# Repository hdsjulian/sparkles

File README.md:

This repo theoretically contains everything to build, assemble and run the sparkling forests light installation. In practice it would require much more documentation which i'm too lazy for right now, and maybe the casing-folder also has some pretty rogue STL files that don't belong there.

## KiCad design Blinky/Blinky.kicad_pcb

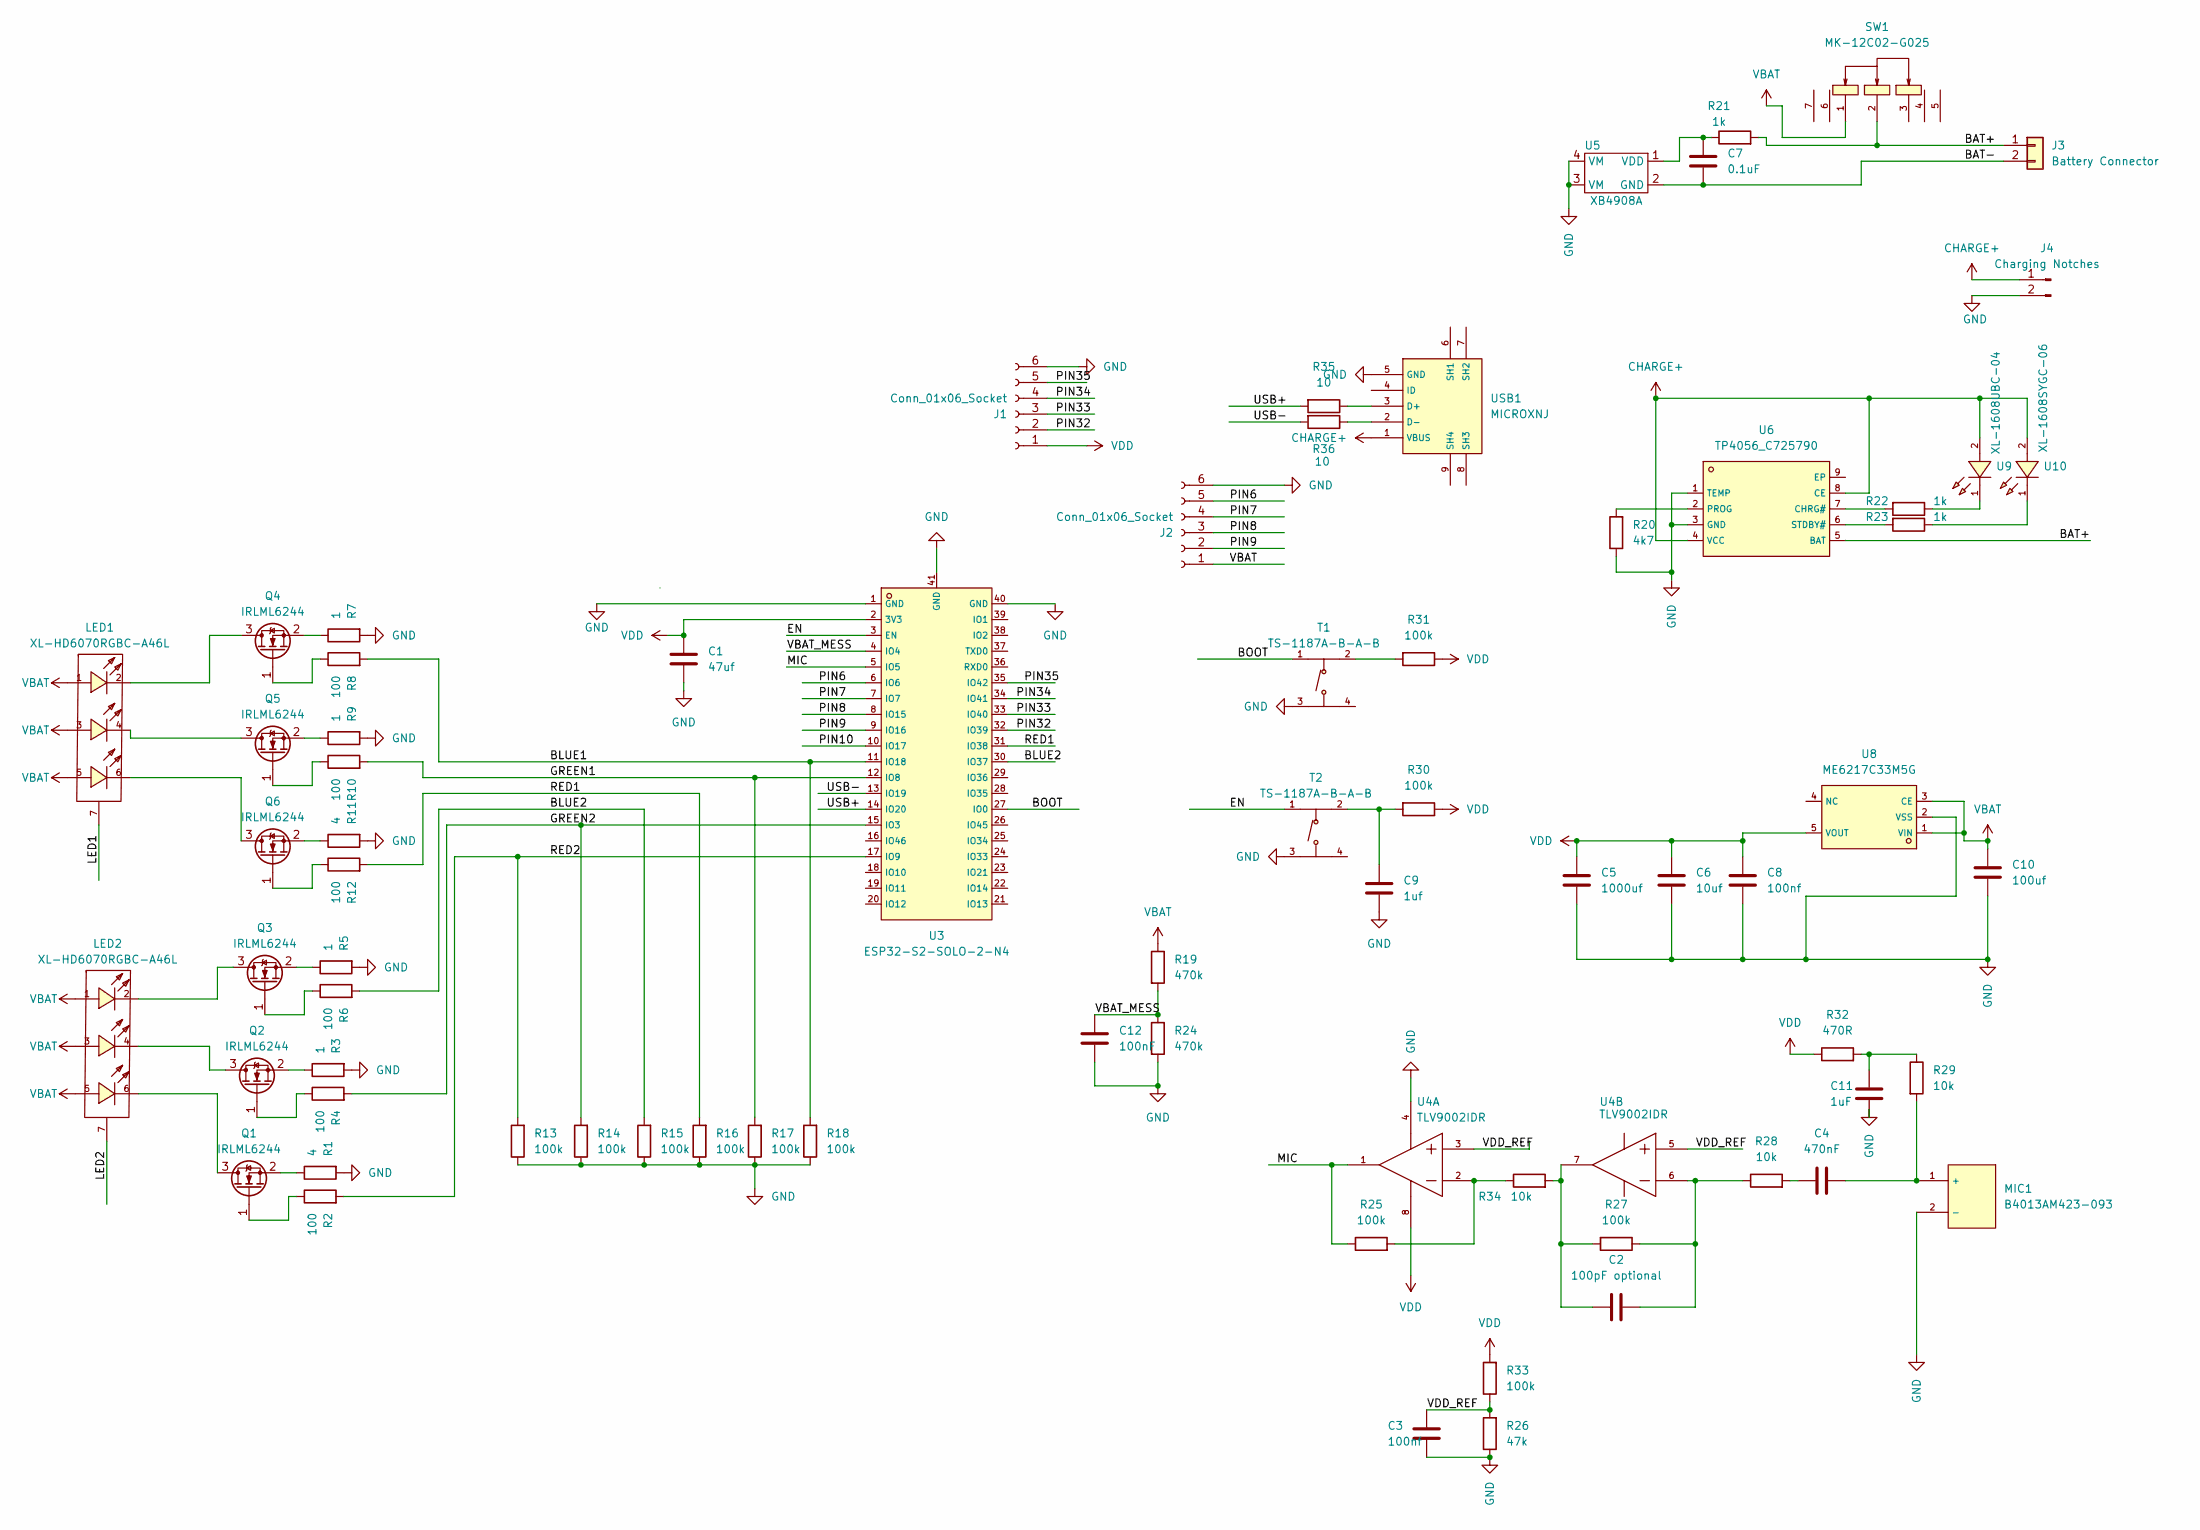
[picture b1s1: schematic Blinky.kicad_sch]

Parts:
C1: 47uf; C_0603_1608Metric
C2: 100pF optional; C_0603_1608Metric
C3, C8: 100nf; C_0603_1608Metric
C4: 470nF; C_0603_1608Metric
C5: 1000uf; CAP-SMD_BD8.0-L8.3-W8.3-FD
C6: 10uf; C_0603_1608Metric
C7: 0.1uF; C_0603_1608Metric
C9: 1uf; C_0603_1608Metric
C10: 100uf; CASE-B_3528
C11: 1uF; C_0603_1608Metric
C12: 100nF; C_0603_1608Metric
J1, J2: Conn_01x06_Socket; HDR-TH_6P-P2.54-V-F
J3: Battery Connector; JST_PH_B2B-PH-K_1x02_P2.00mm_Vertical
J4: Charging Notches; ChargingNotches
LED1, LED2: XL-HD6070RGBC-A46L; LED-SMD_XL-HD6070RGBC-A46L; LCSC C5349977
MIC1: B4013AM423-093; MIC-TH_BD6.0_B6027AP383-056; LCSC C233790
Q1, Q2, Q3, Q4, Q5, Q6: IRLML6244; SOT-23
R1, R11: 4; R_0603_1608Metric
R2, R4, R6, R8, R10, R12: 100; R_0603_1608Metric
R3, R5, R7, R9: 1; R_0603_1608Metric
R13, R14, R15, R16, R17, R18, R25, R27, R30, R31, R33: 100k; R_0603_1608Metric
R19, R24: 470k; R_0603_1608Metric
R20: 4k7; R_0603_1608Metric
R21, R22, R23: 1k; R_0603_1608Metric
R26: 47k; R_0603_1608Metric
R28, R29, R34: 10k; R_0603_1608Metric
R32: 470R; R_0603_1608Metric
R35, R36: 10; R_0603_1608Metric
SW1: MK-12C02-G025; SW-SMD_MK-12C02-G025; LCSC C778186
T1, T2: TS-1187A-B-A-B; SW-SMD_4P-L5.1-W5.1-P3.70-LS6.5-TL-2; LCSC C318884
U3: ESP32-S2-SOLO-2-N4; WIRELM-SMD_ESP32-S3-WROOM-1; LCSC C3040594
U4: TLV9002IDR; SOIC-8_L4.9-W3.9-P1.27-LS6.0-BL; LCSC C398360
U5: XB4908A
U6: TP4056_C725790; ESOP-8_L4.9-W3.9-P1.27-LS6.0-BL-EP; LCSC C725790
U8: ME6217C33M5G; SOT-23-5_L3.0-W1.7-P0.95-LS2.8-BR; LCSC C427602
U9: XL-1608UBC-04; LED0603-RD_BLUE; LCSC C965807
U10: XL-1608SYGC-06; LED0603-RD_GREEN; LCSC C965805
USB1: MICROXNJ; MICRO-USB-SMD_MICROXNJ; LCSC C404969

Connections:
/BAT+: J3.1, R21.2, SW1.2, U6.5 (BAT)
/BAT-: C7.2, J3.2, U5.2 (GND)
/BLUE1: R8.2, R18.2, U3.11 (IO18)
/BLUE2: R6.2, R15.2, U3.30 (IO37)
/BOOT: T1.1 (A), U3.27 (IO0)
/EN: T2.1 (A), U3.3 (EN)
/GREEN1: R10.2, R17.2, U3.12 (IO8)
/GREEN2: R4.2, R14.2, U3.15 (IO3)
/LED1: LED1.7
/LED2: LED2.7
/MIC: R25.1, U3.5 (IO5), U4.1 (OUT1)
/PIN6: J2.5, U3.6 (IO6)
/PIN7: J2.4, U3.7 (IO7)
/PIN8: J2.3, U3.8 (IO15)
/PIN9: J2.2, U3.9 (IO16)
/PIN10: U3.10 (IO17)
/PIN32: J1.2, U3.32 (IO39)
/PIN33: J1.3, U3.33 (IO40)
/PIN34: J1.4, U3.34 (IO41)
/PIN35: J1.5, U3.35 (IO42)
/RED1: R12.2, R16.2, U3.31 (IO38)
/RED2: R2.2, R13.2, U3.17 (IO9)
/USB+: R35.2, U3.14 (IO20)
/USB-: R36.2, U3.13 (IO19)
/VBAT_MESS: C12.2, R19.2, R24.1, U3.4 (IO4)
/VDD_REF: C3.1, R26.2, R33.1, U4.3 (IN1+), U4.5 (IN2+)
CHARGE+: J4.1, U6.4 (VCC), U6.8 (CE), U9.2 (A), U10.2 (A), USB1.1 (VBUS)
GND: C1.1, C3.2, C5.2, C6.1, C8.1, C9.1, C10.2, C11.2, C12.1, J1.6, J2.6, J4.2, MIC1.2 (-), R1.2, R3.2, R5.2, R7.2, R9.2, R11.2, R13.1, R14.1, R15.1, R16.1, R17.1, R18.1, R20.1, R24.2, R26.1, T1.3 (C), T2.3 (C), U3.1 (GND), U3.40 (GND), U3.41 (GND), U4.4 (V-), U5.3 (VM), U5.4 (VM), U6.1 (TEMP), U6.3 (GND), U8.2 (VSS), USB1.5 (GND)
unnamed: C4.1, R28.2
unnamed: C11.1, R29.1, R32.2
unnamed: C4.2, MIC1.1 (+), R29.2
unnamed: LED2.6, Q1.3 (D)
unnamed: Q1.1 (G), R2.1
unnamed: Q1.2 (S), R1.1
unnamed: LED2.4, Q2.3 (D)
unnamed: Q2.1 (G), R4.1
unnamed: Q2.2 (S), R3.1
unnamed: LED2.2, Q3.3 (D)
unnamed: Q3.1 (G), R6.1
unnamed: Q3.2 (S), R5.1
unnamed: LED1.2, Q4.3 (D)
unnamed: Q4.1 (G), R8.1
unnamed: Q4.2 (S), R7.1
unnamed: LED1.4, Q5.3 (D)
unnamed: Q5.1 (G), R10.1
unnamed: Q5.2 (S), R9.1
unnamed: LED1.6, Q6.3 (D)
unnamed: Q6.1 (G), R12.1
unnamed: Q6.2 (S), R11.1
unnamed: R31.2, T1.2 (B)
unnamed: C9.2, R30.2, T2.2 (B)
unnamed: R25.2, R34.1, U4.2 (IN1-)
unnamed: C2.2, R27.1, R28.1, U4.6 (IN2-)
unnamed: C2.1, R27.2, R34.2, U4.7 (OUT2)
unnamed: C7.1, R21.1, U5.1 (VDD)
unnamed: R22.2, U6.7 (CHRG#)
unnamed: R20.2, U6.2 (PROG)
unnamed: R23.2, U6.6 (STDBY#)
unnamed: R22.1, U9.1 (K)
unnamed: R23.1, U10.1 (K)
unnamed: R35.1, USB1.3 (D+)
unnamed: R36.1, USB1.2 (D-)
VBAT: C10.1, J2.1, LED1.1, LED1.3, LED1.5, LED2.1, LED2.3, LED2.5, R19.1, SW1.1, U8.1 (VIN), U8.3 (CE)
VDD: C1.2, C5.1, C6.2, C8.2, J1.1, R30.1, R31.1, R32.1, R33.2, U3.2 (3V3), U4.8 (V+), U8.5 (VOUT)

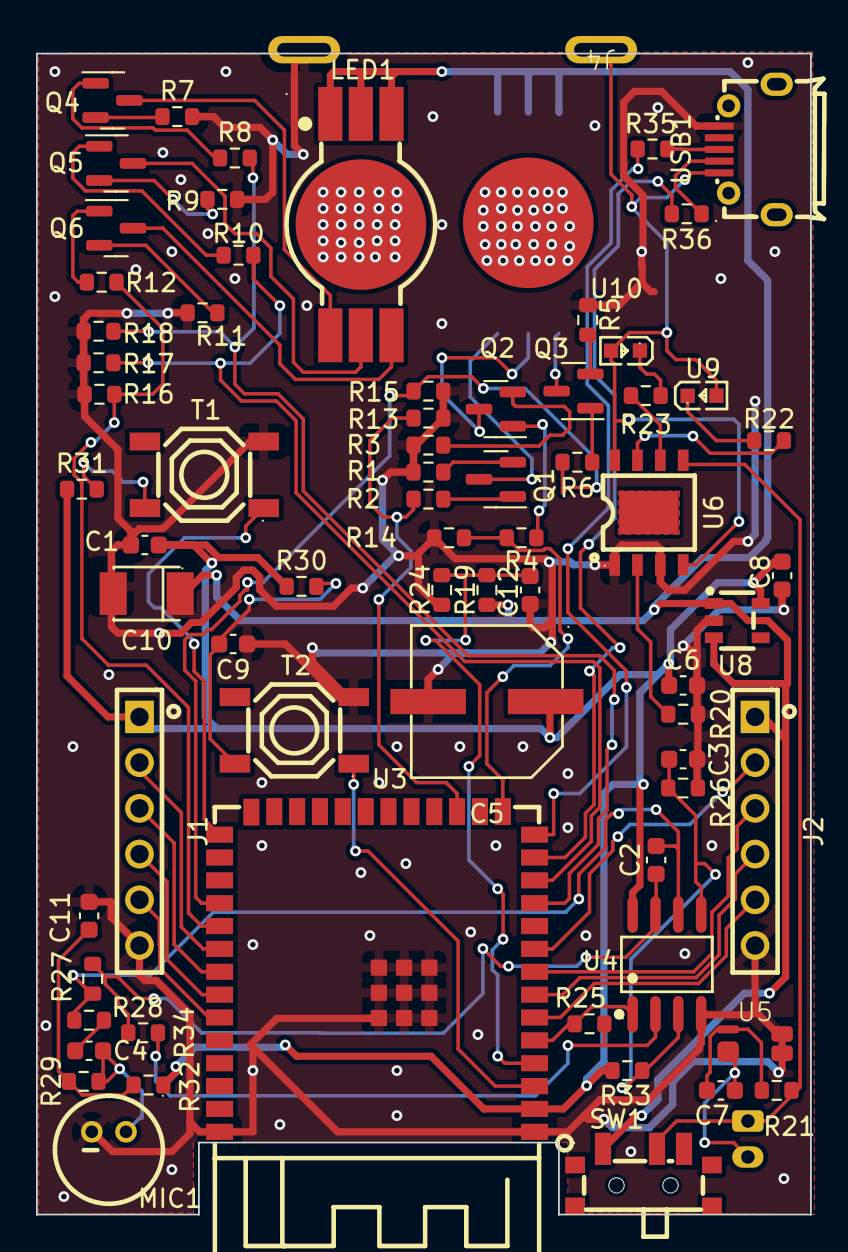
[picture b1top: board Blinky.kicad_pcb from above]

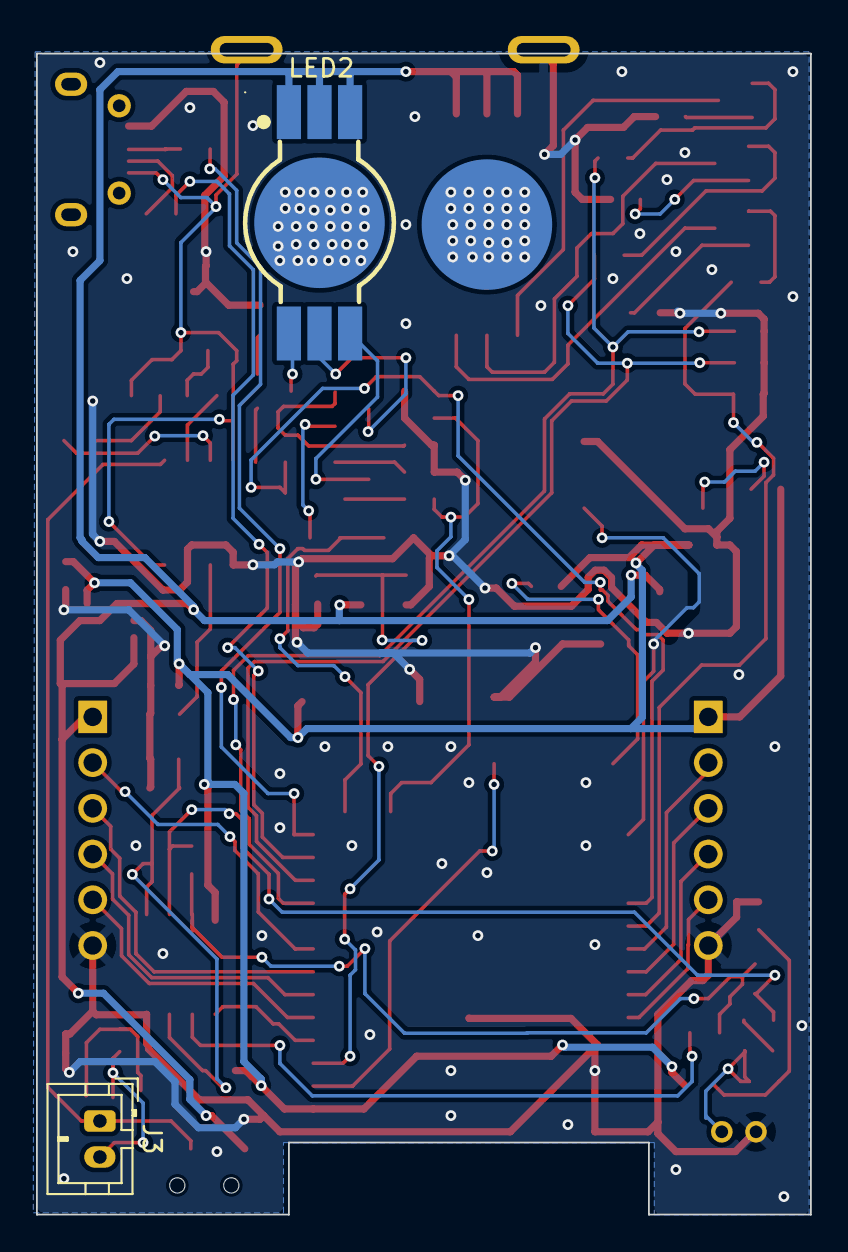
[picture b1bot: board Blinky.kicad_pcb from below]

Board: 2 copper layers, 43.0 x 64.5 mm, 72 parts (2 on the bottom side), 61 nets.

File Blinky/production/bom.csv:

Designator,Footprint,Quantity,Value,LCSC Part #
C1,0603,1,47uf,
C10,CASE-B_3528,1,100uf,
"C11, C9",0603,2,1uF,
"C12, C3, C8",0603,3,100nF,
C2,0603,1,100pF optional,
C4,0603,1,470nF,
C5,CAP-SMD_BD8.0-L8.3-W8.3-FD,1,1000uf,
C6,0603,1,10uf,
C7,0603,1,0.1uF,
"J1, J2",HDR-TH_6P-P2.54-V-F,2,Conn_01x06_Socket,
J3,JST_PH_B2B-PH-K_1x02_P2.00mm_Vertical,1,Battery Connector,
J4,ChargingNotches,1,Charging Notches,
"LED1, LED2",LED-SMD_XL-HD6070RGBC-A46L,2,XL-HD6070RGBC-A46L,C5349977
MIC1,MIC-TH_BD6.0_B6027AP383-056,1,B4013AM423-093,C233790
"Q1, Q2, Q3, Q4, Q5, Q6",SOT-23,6,IRLML6244,
"R1, R11",0603,2,4,
"R10, R12, R2, R4, R6, R8",0603,6,100,
"R13, R14, R15, R16, R17, R18, R25, R27, R30, R31, R33",0603,11,100k,
"R19, R24",0603,2,470k,
R20,0603,1,4k7,
"R21, R22, R23",0603,3,1k,
R26,0603,1,47k,
"R28, R29, R34",0603,3,10k,
"R3, R5, R7, R9",0603,4,1,
R32,0603,1,470R,
"R35, R36",0603,2,10,
SW1,SW-SMD_MK-12C02-G025,1,MK-12C02-G025,C778186
"T1, T2",SW-SMD_4P-L5.1-W5.1-P3.70-LS6.5-TL-2,2,TS-1187A-B-A-B,C318884
U10,LED0603-RD_GREEN,1,XL-1608SYGC-06,C965805
U3,WIRELM-SMD_ESP32-S3-WROOM-1,1,ESP32-S2-SOLO-2-N4,C3040594
U4,SOIC-8_L4.9-W3.9-P1.27-LS6.0-BL,1,TLV9002IDR,C398360
U5,XB4908A,1,XB4908A,
U6,ESOP-8_L4.9-W3.9-P1.27-LS6.0-BL-EP,1,TP4056_C725790,C725790
U8,SOT-23-5_L3.0-W1.7-P0.95-LS2.8-BR,1,ME6217C33M5G,C427602
U9,LED0603-RD_BLUE,1,XL-1608UBC-04,C965807
USB1,MICRO-USB-SMD_MICROXNJ,1,MICROXNJ,C404969

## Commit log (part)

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2024-02-03 weird bug
2024-03-28 timer ready
2024-06-28 zwischen
2024-07-04 weird clap device bug
2024-07-14 html fuer ben
2024-07-15 asdf
2024-07-17 reset timer works
2024-07-23 ready to set up?
2024-08-19 nach hochzeit plus hardware check
2024-10-29 pre hamburn checkin
2025-04-06 test
2025-06-22 adding testdevice
2025-07-30 Borderland Version
2025-08-04 Added Hardware
2025-11-23 hamburn comit
2026-05-26 post hedo
2026-05-26 fix: unwrap addresses from getAddressList response, align SSE event names with serial bridge
2026-05-26 fix: add svelte-kit sync to build, pin deps, fix setup script
2026-05-26 fix: run on port 80 with CAP_NET_BIND_SERVICE
2026-05-27 asdfasdf
2026-05-27 fix: rename myDefines.h -> MyDefines.h for case-sensitive Linux filesystem
2026-05-28 setup changed
2026-05-28 fix: add prerender=true for login route in static build
2026-05-28 fix: add placeholder favicon.png to unblock login page prerender
2026-05-28 fix: redirect unauthenticated page requests to / so SvelteKit handles login routing client-side
2026-05-28 pass
2026-05-28 feat: live-update clock fields every second in settings
2026-05-28 feat: serial bridge auto-reconnect + serial disconnection warning banner
2026-05-28 feat: show stale-master warning banner when serial connected but silent
2026-05-28 fix: serial warning banner fixed below nav, push page content down
2026-05-28 fix: reduce request timeout to 4s, push serial stale status via SSE every 10s
2026-05-28 fix: reduce blink startTime offset from 1s to 100ms for faster response
2026-05-28 feat: add interactive system test script covering all API endpoints
2026-05-28 fix: replace micros() with esp_timer_get_time() throughout timing system to prevent 71-minute wrap
2026-05-28 fix: prevent event loop blocking and serial port conflicts during flash
    - serial_bridge: move serial writes to reader thread via send queue so
    bridge.send() never blocks the asyncio event loop
    - serial_bridge: add pause_reconnect flag so reader thread stays off the
    port for the full duration of a firmware flash, not just at the start
    - compile.py: skip recompile if source files unchanged (hash check),
    resume port in finally block after master upload
2026-05-28 fix: remove stale line reference in send() after queue refactor
2026-05-28 feat: add maintenance mode and per-device shimmer to battery page
2026-05-28 feat: add Breath animation — sine-wave breathing with distance-based phase spread
2026-05-28 fix: shimmer button sends candle animation instead of background shimmer
2026-05-28 feat: git pull before compile with 15s timeout
2026-05-29 feat: chirp-device firmware, test mode, continuous candle animation
    - Chirp-Device: standalone ESP32-S3 firmware plays an 8-step pseudo-random
    chirp via PCM5102A I2S DAC, announces to master, runs full client-style
    timer sync (MSG_TIMER → MSG_GOT_TIMER), and broadcasts MSG_CLAP with
    synced timestamps around audio playback
    - Master runClapSync: after hardware-delay measurement, sends TIMER_ARRAY_COUNT+5
    MSG_TIMER packets to chirp device; MSG_GOT_TIMER guard skips addressList
2026-05-29 fix: broadcast CMD_SET_MAX_DISTANCE after calibration and test mode so breath spread works correctly
2026-05-29 fix: return 503 'Master not connected' when serial bridge is down instead of timing out
2026-05-29 fix: skip svelte rebuild in deploy.py if sparkles-ui files unchanged after git pull
2026-05-29 debug: revert master setup debug prints, keep CORE_DEBUG_LEVEL=5
2026-05-29 fix: remove ARDUINO_USB_CDC_ON_BOOT from both master envs
2026-05-29 feat: hue/saturation color picker with live preview on animations page
    Adds HueSatPicker component with gradient sliders and color swatch.
    Wired into Strobe, Candle, Bioluminescence, and Breath sections.
    Also adds ARDUINO_USB_CDC_ON_BOOT=1 to Master_WebserverTest_Pi env.
2026-06-01 feat: LoRa log bridge and test script for T-Beam → T-Deck via Meshtastic serial module
2026-06-01 fix: use /dev/ttyTBeam udev symlink for T-Beam serial port
2026-06-05 esp python
2026-06-05 feat: replace serial with ESPythoNOW in aubioAlgo, port Raspi-Device output logic to Python
2026-06-08 feat: route aubioAlgo output via serial to master instead of ESP-NOW
    aubioAlgo.py now sends JSON commands over serial (/dev/ttyACM0) to the
    master ESP32 instead of broadcasting raw ESP-NOW frames directly. Master
    handles new aubio_shimmer and aubio_midi serial commands, sets
    lastMidiTime to suppress the animation loop while audio is active, and
    broadcasts to all clients via ESP-NOW as before.
2026-06-08 feat: absorb pitchdetector into main repo, replace ESP-NOW with serial
    Moves pitchdetector/ from a standalone git repo into SparklesCurrent.
    aubioAlgo.py now sends JSON over serial to the master ESP32 instead of
    broadcasting raw ESP-NOW frames. Requirements trimmed to only what's
    needed: numpy, aubio, music21, pyaudio, pyserial.
2026-06-08 feat: Pi 5 setup scripts, systemd services, kiosk config
    - setup.sh: master setup script running all steps in order
    - setup/01_system_deps.sh: apt packages (python, audio, kiosk, midi)
    - setup/02_python_deps.sh: virtualenv + pip requirements
    - setup/03_folders.sh: creates songs/ and logs/ directories
    - setup/04_services.sh: installs and enables all systemd services
    - setup/05_kiosk.sh: Chromium kiosk autostart via Openbox
2026-06-08 feat: add nginx reverse proxy on port 80
    Configures nginx to proxy localhost:80 → localhost:8080 with SSE
    support. Kiosk updated to wait on port 80. Setup script installs
    and enables nginx alongside other services.
2026-06-08 fix: use system default locale instead of hardcoding en_US
2026-06-08 fix: install aubio/numpy via apt, use system-site-packages venv
    aubio fails to build from source on Python 3.13/aarch64. Install via
    apt instead and create the venv with --system-site-packages so it can
    use the system aubio and numpy.
2026-06-09 feat: serial_mux logs all TX/RX to serial.log
    serial_mux now owns the serial log file and writes every TX (client→serial)
    and RX (serial→clients) line with timestamp. serial_bridge no longer
    duplicates to the same file.
2026-06-09 feat: add fast resync — parallel pool of 5 concurrent timer syncs
    startFastResyncTask() syncs clients in batches of 5 in parallel,
    cutting resync time from ~1.5min to ~18s for 100 clients. Slow
    sync (startAllTimerSyncTask) retained for post-calibration use.
    Exposed as serial cmd 'sync_fast' and GET /commandSyncFast.
2026-06-09 deploy
2026-06-09 more setup
2026-06-09 fixed paths
2026-06-09 ipv6
2026-06-09 master fix?
2026-06-09 fix: catch socket timeout in client recv loop so send timeout doesn't disconnect clients
2026-06-09 bugfixeds
2026-06-09 sudo
2026-06-09 fix: reduce presync delay from 20s to 5s before strobe/blink
2026-06-09 fix: relax timer sync acceptance thresholds on client
    The 2500us timeDiff and 6000us lastDelay thresholds were too tight,
    causing clients with normal ESP-NOW jitter to reject most timer packets
    and never accumulate the 10 samples needed to send MSG_GOT_TIMER.
    Raised both to 100ms — the sync correctness is determined by the
    offset calculation, not by packet filtering strictness.
2026-06-09 fix: stop animation loop during timer sync to prevent radio interference
    Animation loop was broadcasting ESP-NOW packets concurrently with timer
    sync unicasts, inflating lastDelay ACK times beyond the 6000μs client
    acceptance threshold. Clients were rejecting all timer samples, so
    MSG_GOT_TIMER was never sent and green blink never occurred.
    Fix: delete animationLoopHandle before starting any sync path (MSG_ADDRESS
    handler, startFastResyncTask), restart it after sync completes. Also fix
2026-06-10 synctest
2026-06-10 fix: correct signed/unsigned overflow in client timer offset calculation
    When offsetMultiplier = -1 (client booted before master), multiplying by
    unsigned long long offsetSum promoted -1 to ULLONG_MAX, producing garbage
    offsets. Cast both operands to long long before multiplying.
2026-06-10 fix: use actual query round-trip time for timer test compensation
    Store send timestamp per client when query is dispatched; on response,
    compute half the actual round-trip instead of using the cached sync delay.
2026-06-10 perf: set CORE_DEBUG_LEVEL=0 on master and client production builds
    Silent by default — use /commandSetLogLevel from the UI to enable
    logging on demand. Reduces UART pressure and task latency.
2026-06-14 remove onboard webserver, commit to raspi serial solution
    delete lib/WebServer and the legacy webserver-based master main. rename the
    serial/pi master from Master_WebserverTest-Device to Master-Device and reclaim
    the Master_Device / Master_Pi env names. point compile.py at the new env and paths.
2026-06-15 trim debug logging
    cut ~115 noise log statements: per-packet/per-loop spam, setter echoes, task-start
    breadcrumbs, commented-out and duplicate logs. kept errors, one-shot state
    transitions, OTA, and the json protocol output to the pi. removed two now-empty
    debug helpers (printAllPeers, printAddress).
2026-06-18 master debug instrumentation: loop watchdog, heap reporting, esp_now_send check, coredump-to-uart on Master_Pi
    enableLoopWDT turns a loop() freeze into a panic with backtrace. heap event every
    5s to spot exhaustion. log esp_now_send failures under shimmer load. Master_Pi
    build gets coredump-to-uart for full crash dumps.
2026-06-20 add public karaoke page
    new /karaoke route (no login) lists songs and plays the associated midi file on
    the keyboard via the existing /keyboard endpoints. layout renders it standalone
    like the login page. /karaoke and /keyboard/ made public in the api. stub song
    'pour elise' added as songs/pour_elise.mid (default songs dir).
2026-06-20 karaoke playback also drives the lights
    forward each played note from file playback to the mux, same keyboard_midi path
    live key presses use, so the music device broadcasts them and the clients animate
    in time with the song.
2026-06-20 prettier karaoke page: glowing dark theme, big touch tiles, now-playing equalizer
2026-06-20 update.sh restarts the kiosk browser; kiosk launcher loops so it self-heals and relaunches with the fresh build
2026-06-20 karaoke: 20 numbered pour elise stubs to test scrolling; prettify drops leading zeros
2026-06-20 dim kiosk panel at boot for battery + hide touchscreen scrollbar
    set backlight to a low value in the kiosk autostart (udev rule grants the kiosk
    user write access to /sys/class/backlight), and hide the scrollbar on the karaoke
    page since it is touch-scrolled.
2026-06-20 update.sh: run as julian, use sudo only for service restart (keeps .git julian-owned)
2026-06-20 kiosk idle-blank: use xrandr (DSI output off) since the panel ignores bl_power/brightness
    wake by a blocking read of the touch event device (works while the output is off),
    dropping xprintidle. julian joins the input group to read the device.
2026-06-20 kiosk blanker: match touchscreen by controller name (ft5x06 etc.) not greedy 'ts'; event numbers shuffle across reboots
2026-06-23 kiosk blanker: auto-detect the connected DSI output instead of hardcoding DSI-1 (survives moving the panel between DSI ports)
2026-06-26 kiosk: add missing .xinitrc (exec openbox-session) and console autologin
    without these the login -> startx -> openbox -> chromium chain never starts:
    startx had no xinitrc so it didn't launch openbox, and no autologin meant
    .bash_profile never ran startx. these were manual on the old card.
2026-06-27 Added songs
2026-06-27 add piano_only.py: strip MIDI files to just the piano part for piano karaoke
    keeps GM piano-program channels (0-7), drops drums and other instruments,
    preserves tempo/time-sig. --inspect lists tracks/channels/instruments.
2026-06-27 piano_only: add --keep-channels/--drop-channels for crafting accompaniment tracks
